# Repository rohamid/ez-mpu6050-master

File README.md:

## MPU6050
MPU6050 breakout board module with Stemma QT styles connector. All pinout and I2C connector is similar to Adafruit's MPU6050 breakout board to ensure compatibility. 

### MPU6050 Top

### MPU6050 Bottom

### MPU6050 PCB Dimension

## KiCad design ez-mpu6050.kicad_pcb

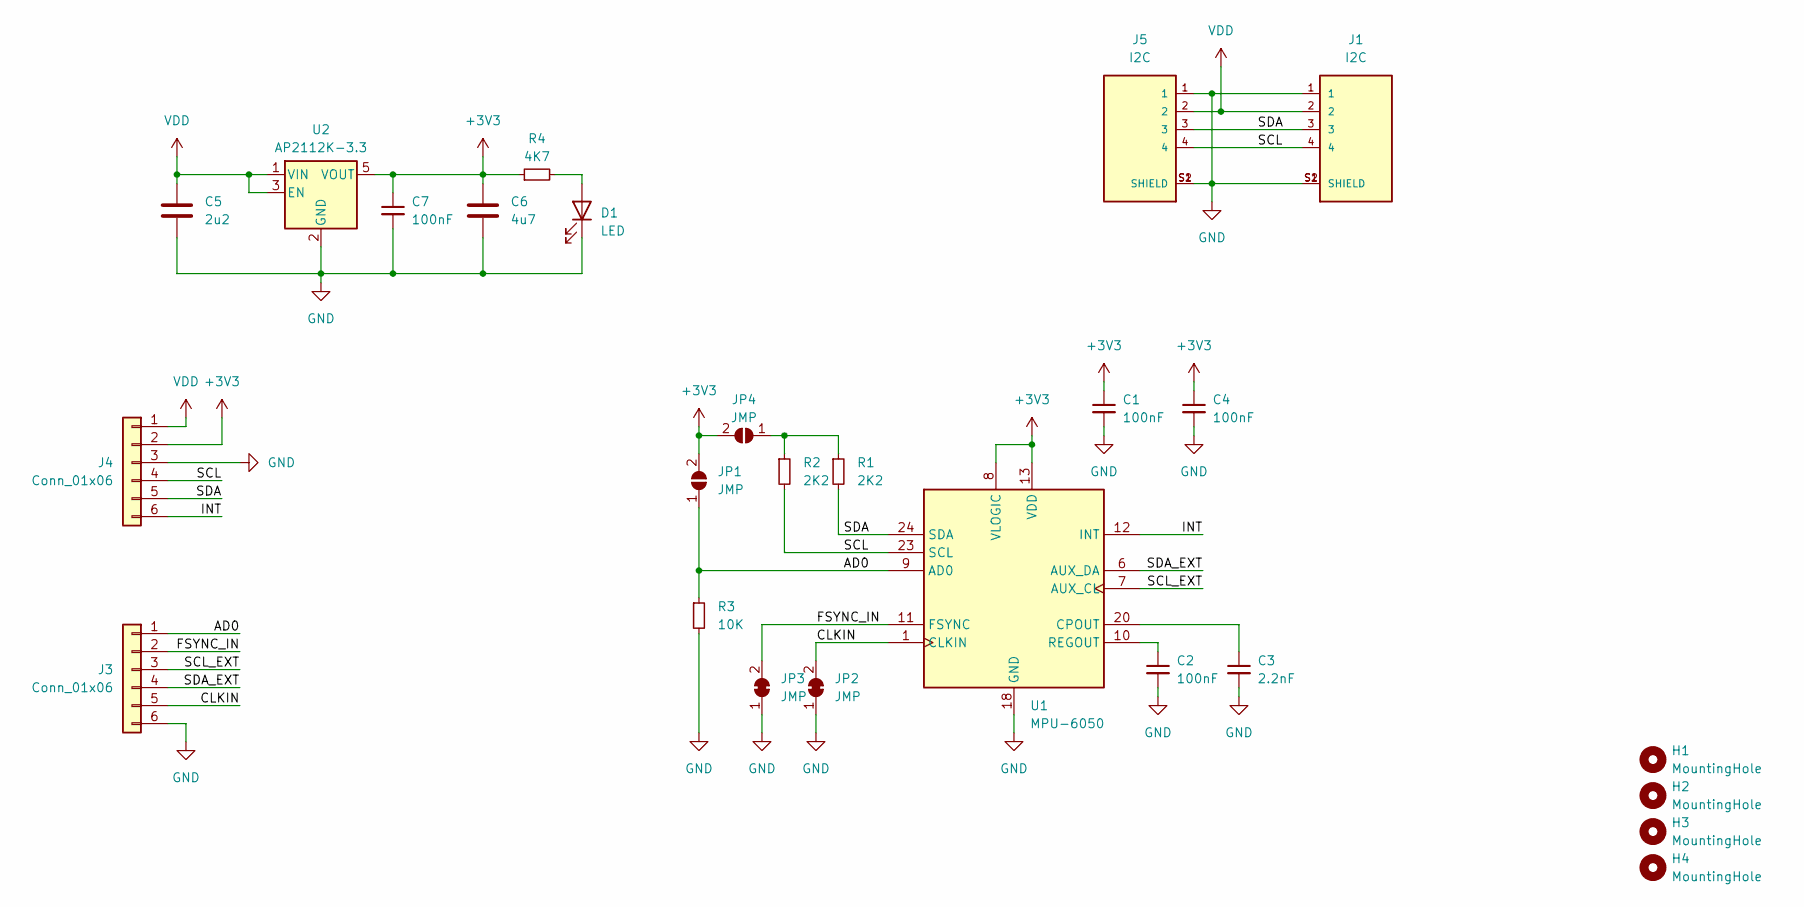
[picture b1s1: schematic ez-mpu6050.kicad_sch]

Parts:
C1, C2, C4, C7: 100nF; C_0402_1005Metric
C3: 2.2nF; C_0402_1005Metric
C5: 2u2; C_0603_1608Metric
C6: 4u7; C_0603_1608Metric
D1: LED; LED_0805_2012Metric
H1, H2, H3, H4: MountingHole; MountingHole_3.2mm_M3
J1, J5: I2C; JST_SM04B-SRSS-TB_LF__SN_
J3, J4: Conn_01x06; PinHeader_1x06_P2.54mm_Vertical
JP1, JP4: JMP; SolderJumper-2_P1.3mm_Open_RoundedPad1.0x1.5mm
JP2, JP3: JMP; SolderJumper-2_P1.3mm_Bridged_RoundedPad1.0x1.5mm
R1, R2: 2K2; R_0402_1005Metric
R3: 10K; R_0402_1005Metric
R4: 4K7; R_0402_1005Metric
U1: MPU-6050; InvenSense_QFN-24_4x4mm_P0.5mm
U2: AP2112K-3.3; SOT-23-5

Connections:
+3V3: C1.1, C4.1, C6.1, C7.1, J4.2, JP1.2 (B), JP4.2 (B), R4.1, U1.8 (VLOGIC), U1.13 (VDD), U2.5 (VOUT)
/AD0: J3.1, JP1.1 (A), R3.1, U1.9 (AD0)
/CLKIN: J3.5, JP2.2 (B), U1.1 (CLKIN)
/FSYNC_IN: J3.2, JP3.2 (B), U1.11 (FSYNC)
/INT: J4.6, U1.12 (INT)
/SCL: J1.4, J4.4, J5.4, R2.2, U1.23 (SCL)
/SCL_EXT: J3.3, U1.7 (AUX_CL)
/SDA: J1.3, J4.5, J5.3, R1.2, U1.24 (SDA)
/SDA_EXT: J3.4, U1.6 (AUX_DA)
GND: C1.2, C2.2, C3.2, C4.2, C5.2, C6.2, C7.2, D1.1 (K), J1.1, J1.S1 (SHIELD), J1.S2 (SHIELD), J3.6, J4.3, J5.1, J5.S1 (SHIELD), J5.S2 (SHIELD), JP2.1 (A), JP3.1 (A), R3.2, U1.18 (GND), U2.2 (GND)
unnamed: D1.2 (A), R4.2
unnamed: JP4.1 (A), R1.1, R2.1
unnamed: C3.1, U1.20 (CPOUT)
unnamed: C2.1, U1.10 (REGOUT)
VDD: C5.1, J1.2, J4.1, J5.2, U2.1 (VIN), U2.3 (EN)

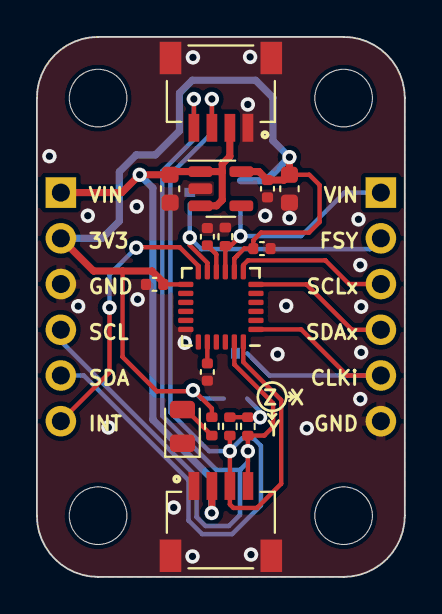
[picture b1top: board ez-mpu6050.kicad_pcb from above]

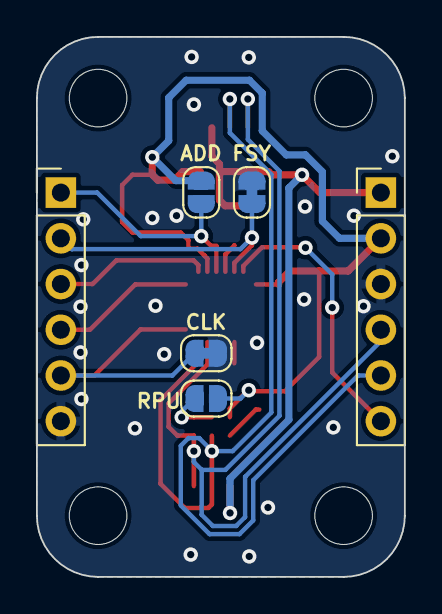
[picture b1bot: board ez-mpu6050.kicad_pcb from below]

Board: 2 copper layers, 20.4 x 30.0 mm, 26 parts (6 on the bottom side), 15 nets.

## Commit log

2024-02-10 Finish tracks add zone & GND vias
2024-02-10 add README
2024-02-12 Add RPU enable jumper
